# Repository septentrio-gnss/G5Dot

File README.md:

# G5Dot

| Role        | Contact                                                                 |
|-------------|-------------------------------------------------------------------------|
| Author      | [laekaz](https://github.com/laekaz)                                     |
| Maintainer  | [Septentrio GNSS GitHub User](githubuser@septentrio.com)                |
| License     | Open-Source Hardware License (CERN-OHL)                                 |

This open source project is derived from the following original project located [here](https://github.com/anavsgmbh/M2_Mosaic-G5_Smart/tree/main)

# Table of Contents
* [Introduction to G5Dot](#introduction-to-g5dot)
  * [What is a G5Dot?](#what-is-a-g5dot)
  * [Who is Septentrio?](#who-is-septentrio)
  * [Where can I buy it?](#where-can-i-buy-it)
    * [Who is ANavS GmbH?](#who-is-anavs-gmbh)
* [Technology](#technology)
  * [What is a mosaic-G5 module?](#what-is-a-mosaic-g5-module)
  * [Other mosaic-G5 versions](#other-mosaic-g5-versions)
* [Why Open Source](#why-open-source)
* [Disclaimer](#disclaimer)
* [How to Produce](#how-to-produce)
  * [Deliverables](#deliverables)
  * [Ordering the mosaic-G5 Module](#ordering-mosaic-g5-module)
* [M.2 Form Factor](#m2-form-factor)
  * [Why M.2?](#why-m2)
  * [Why for NVIDIA?](#why-for-nvidia)
* [User Documentation](#user-documentation)
  * [Interfaces](#interfaces)
  * [Insert in NVIDIA Orin Development Kit](#insert-in-nvidia-orin-development-kit)
  * [Pinout for M.2 Key A+E Connector](#pinout-for-m2-key_ae-connector)
  * [Pinout for mosaic-G5 Module](#pinout-for-mosaic-g5-module)
  * [Antenna](#antenna)
  * [How to Get GNSS Data](#how-to-get-gnss-data)

* [Interface, Protocol & Electrical Specifications](#interface-protocol--electrical-specifications)

# Introduction to G5Dot
## What is a G5Dot?

This is a compact, high precision GNSS (Global Navigation Satellite System) receiver card design for embedded computing platforms, ideal for industrial PCs such as NVIDIA Jetson. Its small size and low power consumption make it appropriate for applications where space and efficiency are critical. 

The design is based on the mosaic-G5 GNSS receiver, which supports multiple satellite systems and enables centimetre-level positioning accuracy. This open-source board was originally designed by ANavS GmbH.
## Who is Septentrio?

Septentrio is a leading company that designs, manufactures and sells high precision and multi-frequency GPS/GNSS receivers for demanding applications. Septentrio products are used in different industries including automotive, marine, construction, rail, machine control, logistics, precision agriculture, geographic information systems (GIS), Unmanned aerial vehicles (UAVs), survey, mapping and scientific applications. Septentrio’s receivers constantly deliver highly accurate and precise GNSS positioning, scalable to centimetre-level and designed to perform perfectly in challenging environments. 

Septentrio's technology offers high accuracy and reliability thanks to advanced GNSS algorithms as well as [Advanced interference Monitoring and mitigation (AIM+)](https://www.septentrio.com/en/learn-more/advanced-positioning-technology/aim-anti-jamming-protection) This protects your application against jamming (RF interference) and spoofing (malicious attacks).

For more information about Septentrio products go to [**https://www.septentrio.com/**](https://web.septentrio.com/GH-SSN-home).

## Where can i buy it?
The board is available for purchase from ANavS

Website: https://anavs.com/products/embedded-modules/gnss-card-g5/

### Who is ANavS GmbH
ANavS GmbH is a German company that develops high precision navigation and positioning systems. Their technology combines GNSS, inertial sensors (IMUs), and sensor fusion algorithms to provide accurate location and orientation.

For more details, visit the product page [here](https://anavs.com/products/embedded-modules/gnss-card-g5/) 

# Technology 
## What is a mosaic-G5 module?
The mosaic-G5 is a compact GNSS receiver module from Septentrio, engineered for high reliability and precise positioning. It integrates the latest multi-band, multi-constellation GNSS technology, providing accurate positions while minimizing power consumption. The receiver can access signals from all major satellite constellations, including GPS, Galileo, GLONASS, and BeiDou.

Different versions of the mosaic-G5 are available to suit various applications, as summarized below:

| Features     | [mosaic-G5 P1](https://www.septentrio.com/en/products/gnss-receivers/gnss-receiver-modules/mosaic-g5-p1) | [mosaic-G5 P3](https://www.septentrio.com/en/products/gnss-receivers/gnss-receiver-modules/mosaic-G5-P3) | [mosaic-G5 P3H](https://www.septentrio.com/en/products/gnss-receivers/gnss-receiver-modules/mosaic-G5-P3H) |
|--------------|--------------|--------------|---------------|
| Functionality|High-precision positioning   |High-precision positioning |Positioning + Heading|
| Use case     |Robotics (e.g robotic mowers), GIS devices |UAV, Commercial mowers, Industrial Robotics, GIS and mapping applications |UAV, Commercial mowers, Industrial Robotics,GIS, mapping applications, sensor fusion and INS systems|             
| GNSS bands   | Triple-band  | Quad-band    | Quad-band     |
| RTK support  | Yes          | Yes          | Yes           |
| Dual antenna |              |              | Yes           |
| Heading      |              |              | Yes           |

## Other mosaic-G5 versions
 You can use other [mosaic modules](https://www.septentrio.com/en/products/gnss-receivers?f%5B0%5D=type%3A604), but you need to pay attention to the functions and pins that could be exposed, then modify the design for your own project. 

## Why open-source 
This board is open-source to encourage collaboration, customization, and innovation. It makes it easy for developers, hobbyists, and integrators to combine high-precision GNSS positioning with platforms like NVIDIA, experiment, create spin-off projects, and adapt it for a wide range of robotics, autonomous systems, or industrial applications.

Open-source promotes shared development, letting users build on existing work and push the technology further. It also means you have access to editable design files and are free to modify, build or sell your own version.

## Disclaimer
This project is offered as-is. The main interfaces have been tested, but the design has not been fully checked or approved by the author or Septentrio. You are responsible for how you use it in your own projects. For guidance on working with Septentrio’s GNSS mosaic modules, we suggest reaching out to Septentrio directly.

Support website: https://www.septentrio.com/en/support

# How to produce
## Deliverables
This open-source project contains the following files for designers, producers and integrators around Septentrio's mosaic modules.

Both **Altium Designer** and **KiCad** design files are provided. You can choose either format according to your preferred PCB design workflow.

### Altium Designer

|Files                                    |Description                       |                        
|-----------------------------------------|----------------------------------|
|[G5Dot.PrjPcb](/G5Dot/G5Dot/G5Dot.PrjPcb)                             |Altium Project                    |
|[Cover_Page.SchDoc](/G5Dot/G5Dot/Cover_Page.SchDoc)                        |Cover page                        |
|[M.2_Key_A+E.SchDoc](/G5Dot/G5Dot/M.2_Key_A+E.SchDoc)                       |Schematics for M.2 KEY A+E        |
|[Mosaic-G5.SchDoc](/G5Dot/G5Dot/Mosaic-G5.SchDoc)                         |Schematics for mosaic-G5 P3 module|
|[G5Dot.PrjPcbVariants](/G5Dot/G5Dot/G5Dot.PrjPcbVariants)                   |Introduction and variants         |
|[BOM_G5Dot_REV_01.01_VARIANT_Mosaic-G5_P3H.xlsx](/BOM_G5Dot_REV_01.01_VARIANT_Mosaic-G5_P3H.xlsx)|Bill of Materials   |
|[G5Dot_Schematics.pdf](/G5Dot_Schematics.pdf)                                |Schematics PDF                    |

### KiCad

| File | Description |
|------|-------------|
| [G5Dot.kicad_pro](./G5Dot/G5Dot%20Kicad/G5Dot.kicad_pro) | KiCad project |
| [Cover_Page.kicad_sch](./G5Dot/G5Dot%20Kicad/Cover_Page.kicad_sch) | Cover page schematic |
| [M.2_Key_A+E.kicad_sch](./G5Dot/G5Dot%20Kicad/M.2_Key_A+E.kicad_sch) | Schematics for the M.2 Key A+E interface |
| [Mosaic-G5.kicad_sch](./G5Dot/G5Dot%20Kicad/Mosaic-G5.kicad_sch) | Schematics for the mosaic-G5 P3 module |

## Ordering mosaic-G5 module

You can order the mosaics from Digi-Key, or you can contact Septentrio directly.

| mosaic-G5 versions | Septentrio | Digi-Key part_number|       CompoTEK             |
|--------------------|------------|---------------------|----------------------------|
| mosaic-G5 P1       |[Septentrio_G5-P1](https://www.septentrio.com/en/products/gnss-receivers/gnss-receiver-modules/mosaic-g5-p1) | - |-|
| mosaic-G5 P3       | [Septentrio_G5-P3](https://www.septentrio.com/en/products/gnss-receivers/gnss-receiver-modules/mosaic-G5-P3) | [410501](https://www.digikey.com/en/products/detail/septentrio-inc/410501/28527327) | [sep_mosaic-G5_P3](https://shop.compotek.de/products/mosaic-G5-P3-p789238026)|
| mosaic-G5 P3H      |[Septentrio_G5-P3H](https://www.septentrio.com/en/products/gnss-receivers/gnss-receiver-modules/mosaic-G5-P3H) | [410502](https://www.digikey.com/en/products/detail/septentrio-inc/410502/28527213) | [sep_mosaic-G5_P3H](https://shop.compotek.de/products/mosaic-G5-P3H-p790005981)|
|G5Dot|     -        | [100040](https://www.digikey.com/en/products/detail/anavs-gmbh/100040/28164182) |-   |

# M.2 form factor
## Why M.2?
M.2 form factor is a standard interface used to provide a compact and flexible way to add extra functionality without redesigning the hardware. It is usually used in Laptops for Wi-Fi or SSDs, industrial PCs and embedded boards such as NVIDIA Jetson. 

The M.2 Key A+E connector can fit into a Key E and Key A slots. Key A and Key E modules are mechanically compatible with both Key A and Key E slots.  

## Why for NVIDIA?
NVIDIA Jetson boards are small powerful AI computers designed for applications like robotics, drones and smart systems. They provide powerful GPU performance in a compact, energy-efficient system, making them ideal for real-time AI and embedded development.

Using the M.2 form factor for the mosaic-G5, allows developers already working in the NVIDIA ecosystem to easily add the GNSS module without redesigning their hardware.

# User documentation

## Interfaces

## Insert in NVIDIA Orin development kit
G5Dot can be easily connected to the NVIDIA Jetson board as shown: 

You can insert the board on the underside of the NVIDIA Jetson board 

## Pinout for M.2 Key_A+E Connector 

| Pin #     |Signal to the mosaic module|
|-----------|------------------|
| 3	        |USB D+            |
| 5	        |USB D-            |
| 2,4,72,74	|power 3.3 V       |
| 6         |External LED      | 
| 16        | External LED     | 
| GND	      |GND               |

* USB: the USB interface handles both data communication and receiver configurations. Through this connection, the GNSS receiver module can send positioning data, satellite information, and timing messages.

* Power: the board is powered via 3.3 V supply lines on multiple pins to ensure stable operation. A clean and stable power source is important for reliable GNSS performance.

* LED: these pins can be used to drive external LEDs, which are helpful for quick visual feedback

## Pinout for mosaic-G5 module

| Pin # |mosaic module signals|
|-------|---------------------|
|2      |Antenna              |
|5      |Antenna              |
|12	    |USB D+               |
|13     |USB D-               |
|14     |VBUS                 |
|42     | Pulse Per Second    |
|44, 45 |power 3.3 V          |
|52     |External LED         | 
|53     | External LED        | 
|54     |Antenna power 3.3 V  |
| GND	  |GND                  |

## Antenna

The board exposes two RP-UMRF (micro RF) antenna connectors for GNSS signal reception. These connectors are designed for 50 Ω antennas and provide the interface for connecting external GNSS antennas to the module.

The connectors typically serve as MAIN (primary) and AUX (secondary) inputs, enabling support for advanced features such as dual-band reception and high-precision positioning (e.g., RTK)

## How to get GNSS Data
* Insert the G5Dot into the M.2 slot.
* Connect the GNSS antenna to the antenna connector
* Configure the receiver 

## Interface, Protocol & Electrical Specifications
Interface
* USB (device 2.0 HS up to 480 Mbps)
* Configure PPS via the u.FL connector

Protocols
* SBF (Septentrio Binary Format)
* NMEA
* RTCM v3.x (MSM included)

The official Septentrio mosaic-G5 driver can be used

Electrical
* Input voltage: 3.3 V +/- 5%
* Power consumption:
 * Typical: 0.4-0.6 W 
 * Max: 0.9 W 
* Antenna bias voltage: 3.3 V

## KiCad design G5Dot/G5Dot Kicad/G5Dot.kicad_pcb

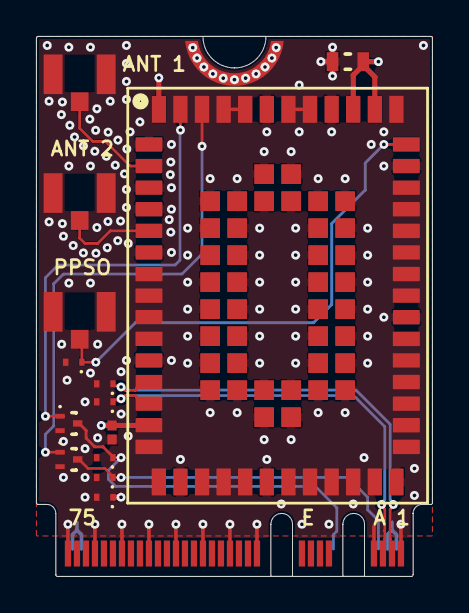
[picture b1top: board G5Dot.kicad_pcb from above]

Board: 4 copper layers, 22.0 x 30.0 mm, 16 parts (0 on the bottom side), 13 nets.

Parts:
C1: C1608X5R0J226M080AC; CAPC1608X100X20ML10
C2: GCM155R71H104KE02D; CAP0402C
D1, D2, D3, D4, D5, D6: ESD9R3.3ST5G; ONSC-SOD-923-2-514AB-01_V
J1: M.2 Dual Key A+E; M.2 Key A+E card-Footprint
J2, J3, J4: 636101112001; 63610111x001
MH1: M.2 Mechanical Ground Pad; M.2 Mechanical Ground Pad Footprint
Q1, Q2: NTK3043NT1G; ONSC-SOT-723-3-631AA-01_V
U1: mosaic-G5-GENERIC; mosaic-G5-GENERIC-Footprint

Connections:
+3.3V: C1.2, C2.2, D3.1, J1.2, J1.4, J1.72, J1.74, U1.14, U1.44, U1.45, U1.54
GND: C1.1, C2.1, D1.2, D2.2, D3.2, D4.2, D5.2, D6.2, J1.1, J1.7, J1.33, J1.39, J1.45, J1.51, J1.57, J1.63, J1.69, J1.75, J2.2, J2.3, J3.2, J3.3, J4.2, J4.3, MH1.0, Q1.2, Q2.2, U1.1, U1.3, U1.4, U1.6, U1.11, U1.17, U1.21, U1.27, U1.34, U1.41, U1.46, U1.49, U1.55, U1.56, U1.57, U1.58, U1.59, U1.60, U1.61, U1.62, U1.63, U1.64, U1.65, U1.66, U1.67, U1.68, U1.69, U1.70, U1.71, U1.72, U1.73, U1.74, U1.75, U1.76, U1.77, U1.78, U1.79, U1.80, U1.81, U1.82, U1.83, U1.84, U1.85, U1.86, U1.87, U1.88, U1.89, U1.90, U1.91, U1.92, U1.93, U1.94
Led1: Q1.1, U1.52
Led2: Q2.1, U1.53
NetD4_1: D4.1, J1.16, Q2.3
NetD5_1: D5.1, J1.6, Q1.3
NetD6_1: D6.1, J4.1, U1.42
NetJ2_1: J2.1, U1.2
NetJ3_1: J3.1, U1.5
NetU1_47: U1.47, U1.48
NetU1_50: U1.50, U1.51
USB_N: D2.1, J1.5, U1.13
USB_P: D1.1, J1.3, U1.12

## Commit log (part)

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2026-03-05 Upload
2026-03-07 Main picture
2026-03-07 Inserting pictures
2026-03-13 HW files update
2026-03-17 Update feedback
2026-03-17 update pictures
2026-03-18 SAME FILES
2026-03-18 bom addition
2026-03-19 logo
2026-03-24 KiCAD update
2026-04-15 updated pictures
2026-04-15 updating project name
2026-04-15 HW files update logo
2026-04-15 update hw files
2026-04-15 hw files update name
2026-04-20 HW file update
2026-06-04 CompoTEK addition

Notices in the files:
G5Dot/G5Dot Kicad/G5Dot.kicad_pcb:
${COPYRIGHT, REV .FAB_REVISION}
